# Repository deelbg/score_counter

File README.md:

# score_counter

[Also available on my online store.](https://www.tindie.com/stores/deyantodorov/)

  Board games Score Counter is a device meant to be used for keeping the score for up to four players when playing board games like Scrabble etc. The numbers of players is selectable through the settings menu. Names up to ten characters long can be entered for each player.
  For each player an accumulated score is stored, which is the total amount of points up to the current moment in the game, and the points from the current round are entered using a rotary encoder or the Up and Down arrow keys. When OK is pressed the point from the current round are added to the total amount. 
  More detailed explanation and screenshot might be found in the User manual [HERE](https://github.com/deelbg/score_counter/blob/master/sc_manual.pdf) or on my web site [HERE](https://deyantodorov.com/2020/06/24/board-games-score-counter/)
  
Main features.
* Small size (10cm / 5.5cm / 1.7cm). 
* Battery powered. Runs on two AAA batteries.
* 1.3” OLED screen.
* Controlled via five buttons and a rotary switch.
* 3D printed enclosure.
* Energy independent memory to store settings and player names.

In the **/firmware** directory is located the firmware. It uses the drivers from my [SSD1306_SH1106_i2c_text_display](https://github.com/deelbg/SSD1306_SH1106_i2c_text_display) and [hal_lib_avr_cpp](https://github.com/deelbg/hal_lib_avr_cpp) repositories. 
The device is based on a Attiny861 microcontroller.

There is a makefile included. Run the folowing:
* make - to build the project
* clean - to delete object files
* size - to see the used RAM and flash.
* flash - to write the .hex file to the microcontroller. Using avrdude and a usbasp programmer.
* eeprom - to write the eeprom.
* fuse - to write the fuses.

In the **/hardware** directory is located the hardware project for EagleCad and a KiCad export. 
**NOTE:** A 10kOhm pullup resistor needs to be added to the OK button (the one right in the center).  

In the **/enclosure** directory is located a FreeCad project containig the enclosure. The 3 parts are also exported in .obj files that can be directly imported in Cura and sliced for 3d printing.

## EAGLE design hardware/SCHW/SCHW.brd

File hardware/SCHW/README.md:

# SCHW
Eagle project for Score Counter

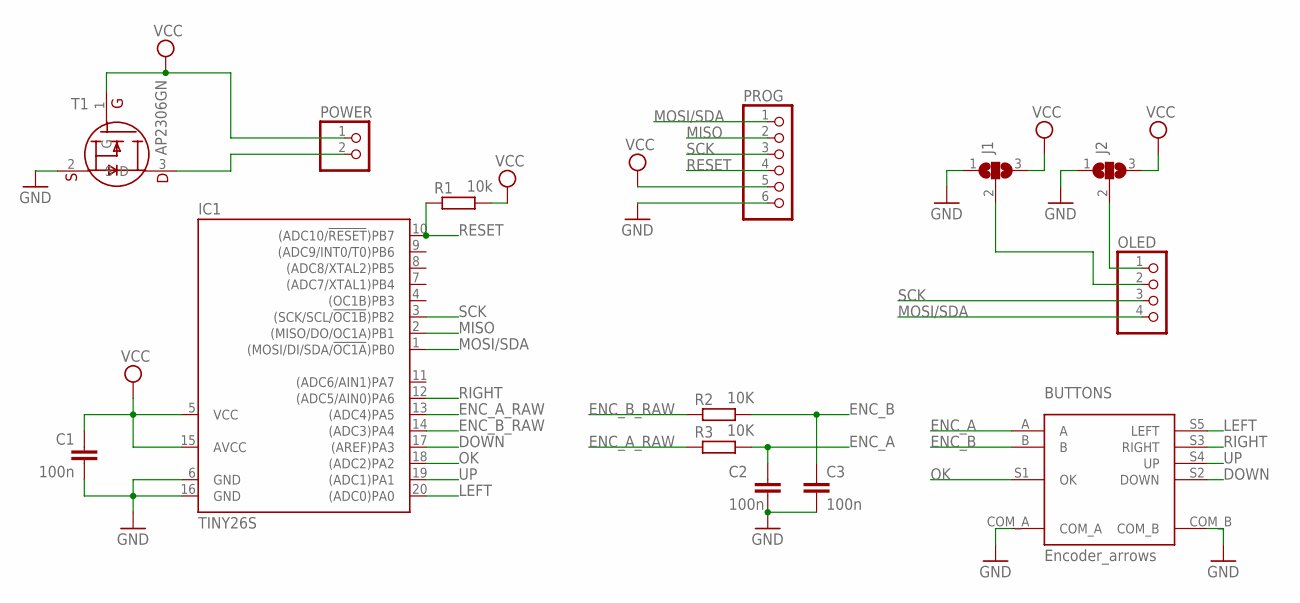
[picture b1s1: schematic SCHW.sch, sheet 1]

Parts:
BUTTONS: ENCODER_ARROWS
C1, C2, C3: 100n; C0805
IC1: TINY26S; SO20L
J1, J2: SJ2W; SJ_2
OLED: PINHD-1X4; 1X04
POWER: PINHD-1X2; 1X02
PROG: PINHD-1X6; 1X06
R1: 10k; R0805
R2, R3: 10K; R0805
T1: AP2306GN_MOSFETSOT23; SOT23

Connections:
DOWN: BUTTONS.S2 (DOWN), IC1.17 ((AREF)PA3)
ENC_A: BUTTONS.A, C2.1, R3.2
ENC_A_RAW: IC1.13 ((ADC4)PA5), R3.1
ENC_B: BUTTONS.B, C3.1, R2.2
ENC_B_RAW: IC1.14 ((ADC3)PA4), R2.1
GND: BUTTONS.COM_A, BUTTONS.COM_B, C1.1, C2.2, C3.2, IC1.6 (GND), IC1.16 (GND), J1.1, J2.1, PROG.6, T1.2 (S)
LEFT: BUTTONS.S5 (LEFT), IC1.20 ((ADC0)PA0)
MISO: IC1.2 ((MISO/DO/OC1A)PB1), PROG.2
MOSI/SDA: IC1.1 ((MOSI/DI/SDA/!OC1A!)PB0), OLED.4, PROG.1
unnamed: POWER.2, T1.3 (D)
unnamed: J2.2, OLED.1
unnamed: J1.2, OLED.2
OK: BUTTONS.S1 (OK), IC1.18 ((ADC2)PA2)
RESET: IC1.10 ((ADC10/!RESET!)PB7), PROG.4, R1.1
RIGHT: BUTTONS.S3 (RIGHT), IC1.12 ((ADC5/AIN0)PA6)
SCK: IC1.3 ((SCK/SCL/!OC1B!)PB2), OLED.3, PROG.3
UP: BUTTONS.S4 (UP), IC1.19 ((ADC1)PA1)
VCC: C1.2, IC1.5 (VCC), IC1.15 (AVCC), J1.3, J2.3, POWER.1, PROG.5, R1.2, T1.1 (G)

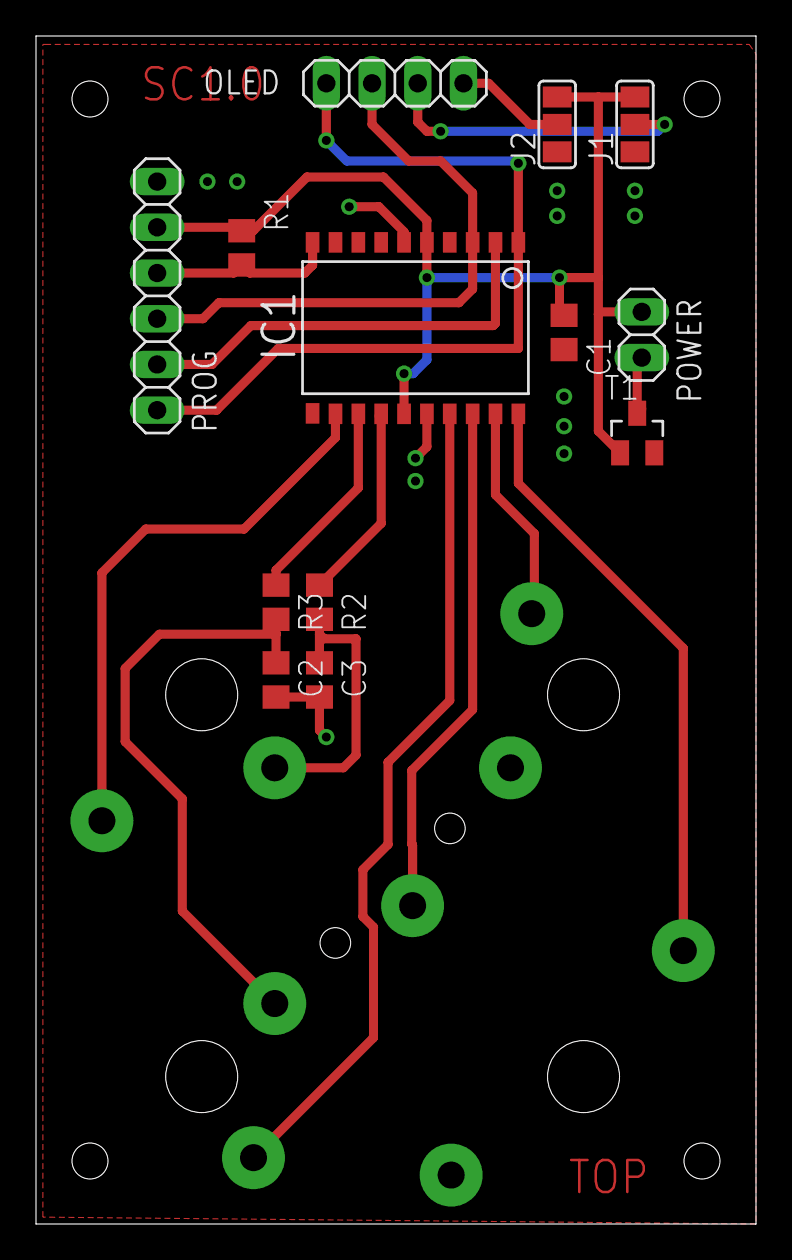
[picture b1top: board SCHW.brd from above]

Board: 2 copper layers, 40.0 x 66.0 mm, 14 parts (1 on the bottom side), 18 nets.

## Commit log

2020-06-25 Score counter, hardware, software and enclosure v1.0
2020-06-25 Add build and dist directtories including the .hx file.
2020-06-26 Add the user manual sc_manual.pdf.
